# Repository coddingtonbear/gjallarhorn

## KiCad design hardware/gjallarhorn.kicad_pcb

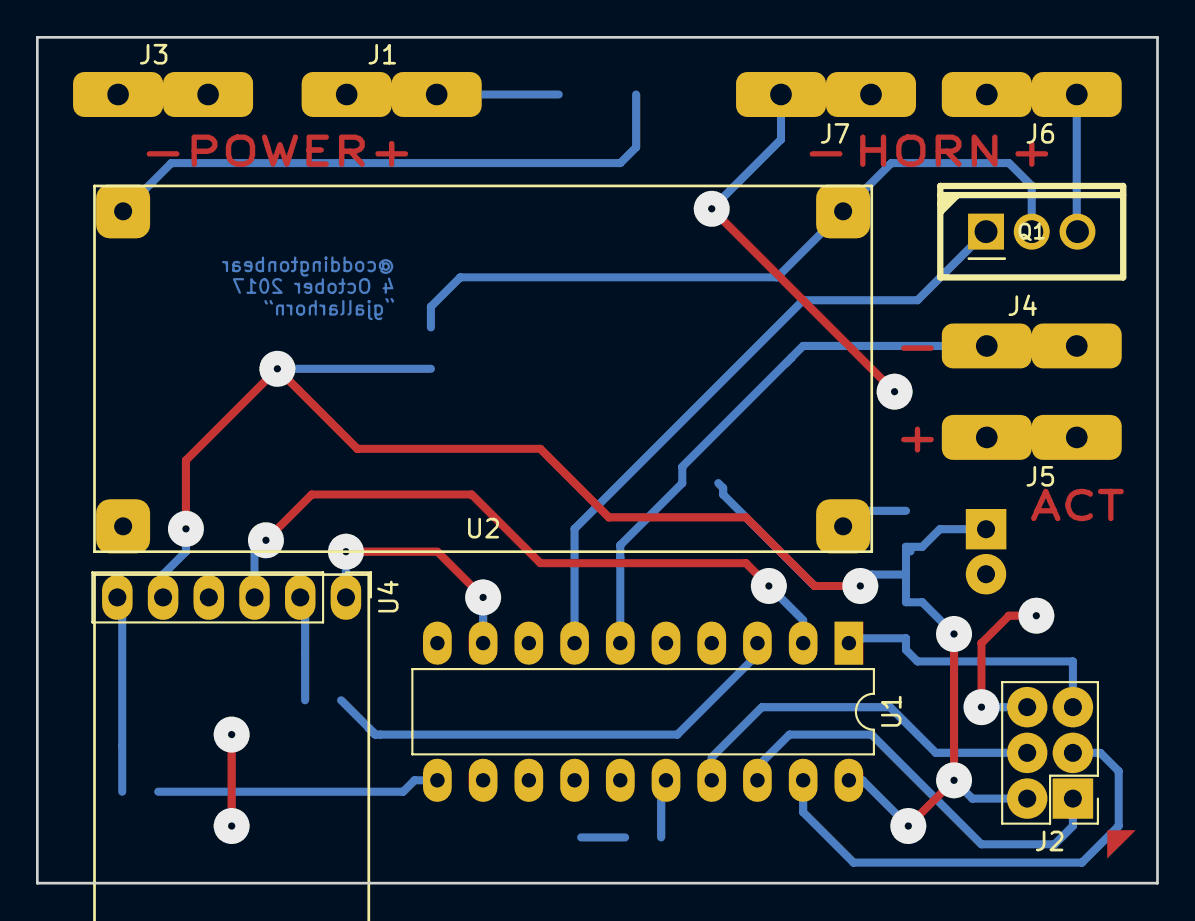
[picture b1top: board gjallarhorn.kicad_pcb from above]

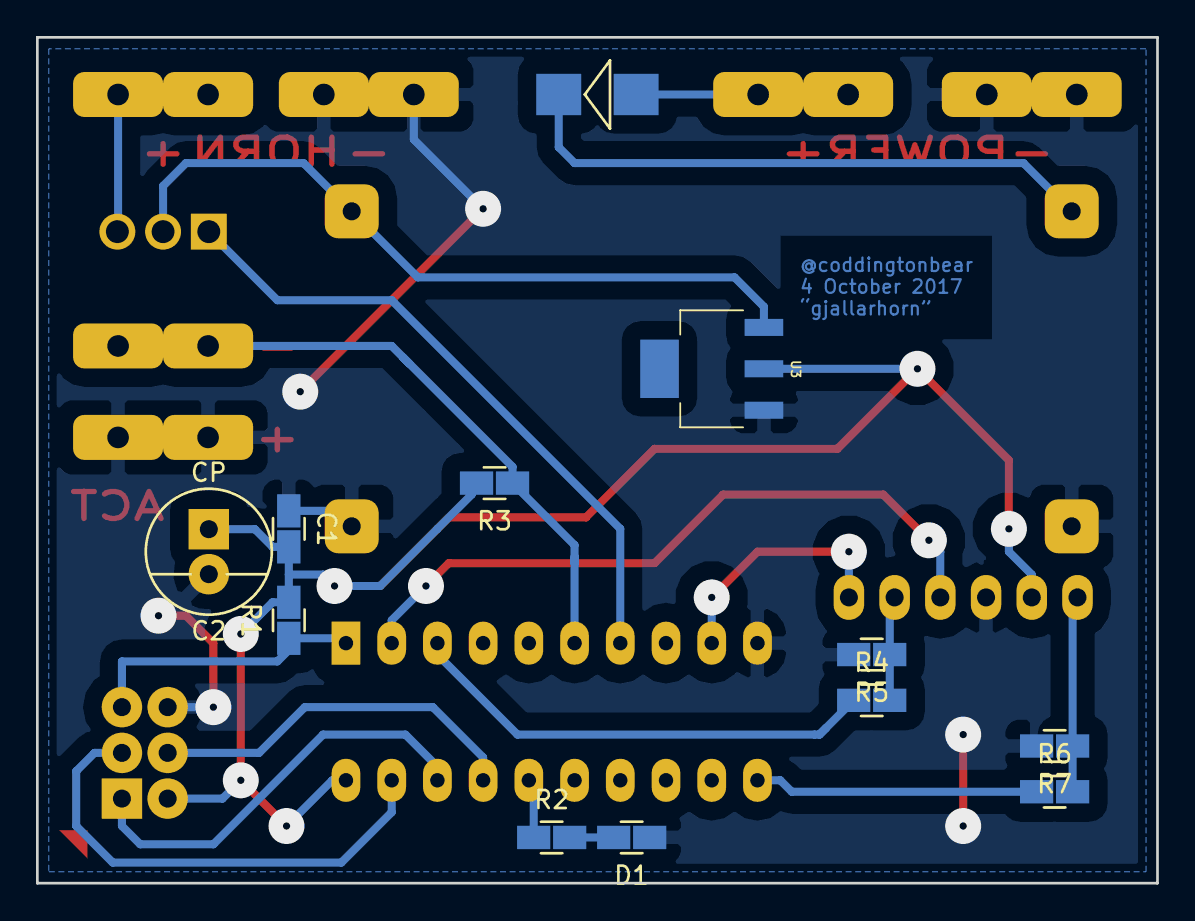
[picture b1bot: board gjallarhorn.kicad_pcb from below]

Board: 2 copper layers, 62.2 x 47.0 mm, 23 parts (12 on the bottom side), 20 nets.

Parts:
C1: 0.1u; 0805_Milling
C2: CP; Capacitor_Electrolytic_D6.3xP2.5
D1: RED; 0805_Milling
D2: D; DO-214AA-SMB
J1: VCC; TAB
J2: PROG; Pin_Header_Straight_2x03_Pitch2.54mm
J3: GND; TAB
J4: BUTTON-; TAB
J5: BUTTON+; TAB
J6: HORN+; TAB
J7: HORN-; TAB
Q1: Q_NMOS_GDS; TO-220
R1, R3, R5, R7: 10k; 0805_Milling
R2: 1k; 0805_Milling
R4, R6: 6.8k; 0805_Milling
U1: ATTINY2313-20PU; DIP-20_W7.62mm_LongPads
U2: BOOST_REGULATOR
U3: AP1117-5.0; SOT-223
U4: HC-05_breakout; Pin_Header_Straight_1x06_Pitch2.54mm

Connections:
+5V: C1.2, C2.1, J2.2, R1.2, R3.2, U1.20, U3.2, U4.5
+12V: Q1.2, U2.3, U3.3
BT_ENABLE: R6.1, U1.11
BT_STATE: U1.9, U4.1
GND: C1.1, C2.2, D1.1, J2.6, J3.1, J5.1, J7.1, R5.2, R7.2, U1.10, U2.2, U2.4, U3.1, U4.4
HORN: Q1.1, U1.7
MISO: J2.1, U1.18
MOSI: J2.4, U1.17
unnamed: D1.2, R2.2
unnamed: D2.1, U2.1
unnamed: D2.2, J1.1
unnamed: J4.1, R3.1, U1.6
unnamed: J6.1, Q1.3
unnamed: R2.1, U1.16
unnamed: R4.2, R5.1, U4.2
unnamed: R6.2, R7.1, U4.6
RESET: J2.5, R1.1, U1.1
RX: U1.2, U4.3
SCK: J2.3, U1.19
TX: R4.1, U1.3

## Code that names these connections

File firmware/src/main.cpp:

#include "main.h"

#define LED_PIN 13
#define ACT_PIN 4

#define HORN_PIN 5

#define BT_STATE_PIN 7
#define BT_ENABLE_PIN 8


#define MAX_ENABLED_MILLIS 5000


bool enabled = false;
bool enabledByButton = false;
unsigned long enabledAt = 0;


void setup() {
    pinMode(LED_PIN, OUTPUT);
    pinMode(ACT_PIN, INPUT);
    pinMode(HORN_PIN, OUTPUT);
    pinMode(BT_ENABLE_PIN, OUTPUT);

    digitalWrite(LED_PIN, LOW);
    digitalWrite(HORN_PIN, LOW);
    digitalWrite(BT_ENABLE_PIN, HIGH);

    digitalWrite(LED_PIN, HIGH);
    delay(1000);
    digitalWrite(LED_PIN, LOW);

    Serial.begin(9600);
}


void loop() {
    bool doEnable = false;
    bool doDisable = false;

    if(Serial.available()) {
        char data = Serial.read();

        Serial.write(data);
        Serial.write('\r');
        Serial.write('\n');

        if(data == '1') {
            doEnable = true;
        } else {
            doDisable = true;
        }
    }
    if(digitalRead(ACT_PIN) == LOW) {
        doEnable = true;
        enabledByButton = true;
    } else if (enabledByButton) {
        doDisable = true;
        enabledByButton = false;
    }

    if(
        enabled &&
        !enabledByButton &&
        (millis() - enabledAt > MAX_ENABLED_MILLIS)
    ) {
        Serial.write("Timeout");
        Serial.write('\r');
        Serial.write('\n');

        doDisable = true;
    }

    if(doEnable) {
        enabled = true;

        digitalWrite(LED_PIN, HIGH);
        digitalWrite(HORN_PIN, HIGH);

        enabledAt = millis();
    } 
    if(doDisable) {
        enabled = false;

        digitalWrite(LED_PIN, LOW);
        digitalWrite(HORN_PIN, LOW);
    }
}

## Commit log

2017-09-26 Adding initial schematic and PCB layout; mostly through-hole now that I'm CNC-ing.
2017-09-26 It would be better if I could fit this in a 60x60 square; let's try (in progress).
2017-09-27 Moving everything everywhere.
2017-10-01 Final version.
2017-10-01 Let's...make a couple more changes.
2017-10-04 Adding mega-basic firmware -- already at 87% full
2017-10-04 Echo output to bluetooth; automatically timeout horn after 5s.
2017-10-05 I guess I can make another?
